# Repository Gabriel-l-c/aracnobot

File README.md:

# 🕷️ Aracnobot - Estrutura de Tarefas

## ⚡ Eletrônica & Código Embarcado (Hardware & Firmware)
- [ ] **Esquema e Layout (KiCad)**
  - [ ] Desenhar o esquemático elétrico (reguladores de tensão e distribuição de potência).
	- [ ] testar os servos e categorizar os angulos limites (para nunca travar em 0 ou 180, o servo nao
	pode travar!!!).
	- [ ] Testar as baterias, descarga, medir o sinal de alimentação da bateria ( tem picos? ruidos?), 
	para analisar necessidade de circuitos de filtro e proteção.
	- [ ] Circuito de BMS (sistema de gerenciamento de bateria), para controle de carregamento, descarga,
	, protecao contra sobrecarga e subtensao.
  - [ ] Fazer o layout da PCB no KiCad (trilhas largas para os servos e definição das pegadas/capacitores).
  - [ ] Gerar arquivos Gerber para fabricação da placa.
  * problemas:
	O banco de baterias disponivel sao 3s2p litio (3 baterias de litio em seria com 1 em parelelo para cada em serie
ou seja, 6 celulas, 3 pares), a descarga maxima das baterias deve ficar em 1.5C ( para uam bateria de 3Ah de capacidade, 
1.5 C =  4.5A de descarga maxima), cada celula tem 4V2 de tensão maxima e 1.5Ah de descarga. Logo, nao conseguimos
alcançar a potência (carga pesada e motores travados, todos sendo usados de uma vez). Dentro disso, temos que 
montar o firmware afim de nunca ultrapassar o consumo de 4.5A total, nao usar todas as patas de uma vez, carga leve, etc.

  - [ ] Circuito do regulador dos motores. Cuidados e problemas:
  A maior parte de potencia sera consumida pelos motores, logo e onde os reguladores vão trabalhar mais e onde mais energia
  sera transformada em calor. Logo, uma pesquisa de reguladores ideias para a carga de tensão de entrada e corrente de saida
  deve ser feita para iniciar o circuito. Reguladores sugestao: K7805, XL4015.
 
- [ ] **Configuração Inicial do Código**
  - [ ] Configurar ambiente de desenvolvimento (PlatformIO, Arduino IDE ou ESP-IDF).
  - [ ] Mapear os pinos físicos da PCB criada para as definições de variáveis no código.
- [ ] **Cinemática e Movimentação junto a equipe de estrutura**
  - [ ] Implementar algoritmo de Cinemática Inversa (IK) para as pernas.
  - [ ] Desenvolver padrões de marcha (Gait Patterns: tripé, onda, etc.).
  - [ ] Criar funções de estabilização corporal integrando sensor IMU/Giroscópio.
- [ ] **Comunicação, Telemetria & Proteção**
  - [ ] Configurar protocolo sem fio (Wi-Fi, Bluetooth ou ESP-NOW) para controle remoto.
  - [ ] Criar rotina de leitura de nível de bateria e alertas de subtensão para proteger as células LiPo.

## 📐 Estrutura Mecânica Física

## 👁️ Visão Computacional & Percepção

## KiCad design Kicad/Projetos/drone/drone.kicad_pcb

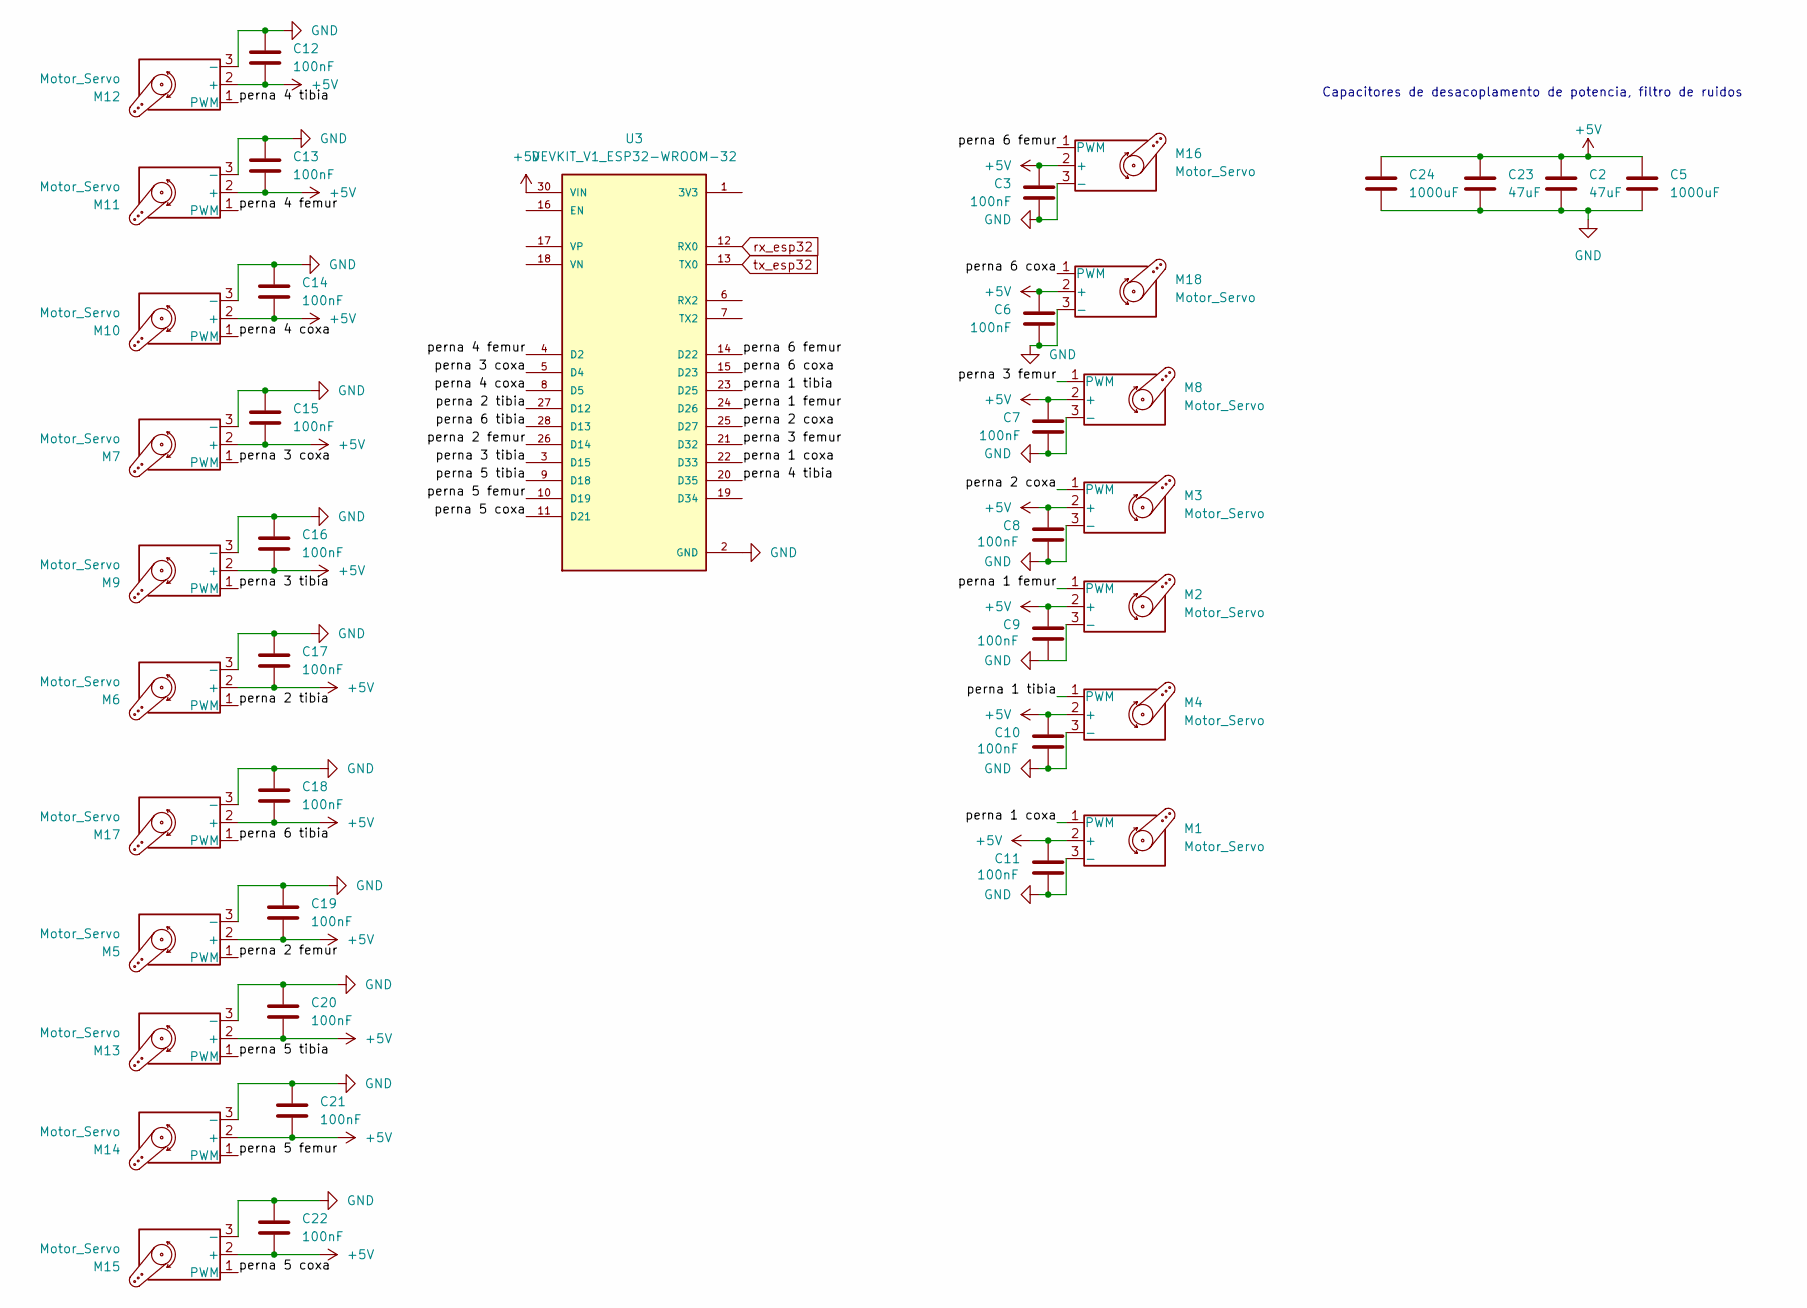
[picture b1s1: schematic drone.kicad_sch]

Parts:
C2, C23: 47uF; C_Disc_D7.0mm_W2.5mm_P5.00mm
C3, C6, C7, C8, C9, C10, C11, C12, C13, C14, C15, C16, C17, C18, C19, C20, C21, C22: 100nF; C_Disc_D7.0mm_W2.5mm_P5.00mm
C5, C24: 1000uF; C_Disc_D7.0mm_W2.5mm_P5.00mm
M1, M2, M3, M4, M5, M6, M7, M8, M9, M10, M11, M12, M13, M14, M15, M16, M17, M18: Motor_Servo; PinHeader_1x03_P2.54mm_Vertical
U3: DEVKIT_V1_ESP32-WROOM-32; MODULE_DEVKIT_V1_ESP32-WROOM-32

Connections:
+5V: C2.1, C3.1, C5.1, C6.1, C7.1, C8.1, C9.1, C10.1, C11.1, C12.2, C13.2, C14.2, C15.2, C16.2, C17.2, C18.2, C19.2, C20.2, C21.2, C22.2, C23.1, C24.1, M1.2 (+), M2.2 (+), M3.2 (+), M4.2 (+), M5.2 (+), M6.2 (+), M7.2 (+), M8.2 (+), M9.2 (+), M10.2 (+), M11.2 (+), M12.2 (+), M13.2 (+), M14.2 (+), M15.2 (+), M16.2 (+), M17.2 (+), M18.2 (+), U3.30 (VIN); also elsewhere on the board
/Raiz/perna 1 coxa: M1.1 (PWM), U3.22 (D33)
/Raiz/perna 1 femur: M2.1 (PWM), U3.24 (D26)
/Raiz/perna 1 tibia: M4.1 (PWM), U3.23 (D25)
/Raiz/perna 2 coxa: M3.1 (PWM), U3.25 (D27)
/Raiz/perna 2 femur: M5.1 (PWM), U3.26 (D14)
/Raiz/perna 2 tibia: M6.1 (PWM), U3.27 (D12)
/Raiz/perna 3 coxa: M7.1 (PWM), U3.5 (D4)
/Raiz/perna 3 femur: M8.1 (PWM), U3.21 (D32)
/Raiz/perna 3 tibia: M9.1 (PWM), U3.3 (D15)
/Raiz/perna 4 coxa: M10.1 (PWM), U3.8 (D5)
/Raiz/perna 4 femur: M11.1 (PWM), U3.4 (D2)
/Raiz/perna 4 tibia: M12.1 (PWM), U3.20 (D35)
/Raiz/perna 5 coxa: M15.1 (PWM), U3.11 (D21)
/Raiz/perna 5 femur: M14.1 (PWM), U3.10 (D19)
/Raiz/perna 5 tibia: M13.1 (PWM), U3.9 (D18)
/Raiz/perna 6 coxa: M18.1 (PWM), U3.15 (D23)
/Raiz/perna 6 femur: M16.1 (PWM), U3.14 (D22)
/Raiz/perna 6 tibia: M17.1 (PWM), U3.28 (D13)
GND: C2.2, C3.2, C5.2, C6.2, C7.2, C8.2, C10.2, C11.2, C12.1, C13.1, C14.1, C15.1, C16.1, C17.1, C18.1, C19.1, C20.1, C21.1, C22.1, C23.2, C24.2, M1.3 (-), M2.3 (-), M3.3 (-), M4.3 (-), M5.3 (-), M6.3 (-), M7.3 (-), M8.3 (-), M9.3 (-), M10.3 (-), M11.3 (-), M12.3 (-), M13.3 (-), M14.3 (-), M15.3 (-), M16.3 (-), M17.3 (-), M18.3 (-), U3.2 (GND), U3.29 (GND); also elsewhere on the board
rx_esp32: U3.12 (RX0); also elsewhere on the board
tx_esp32: U3.13 (TX0); also elsewhere on the board

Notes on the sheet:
Capacitores de desacoplamento de potencia, filtro de ruidos

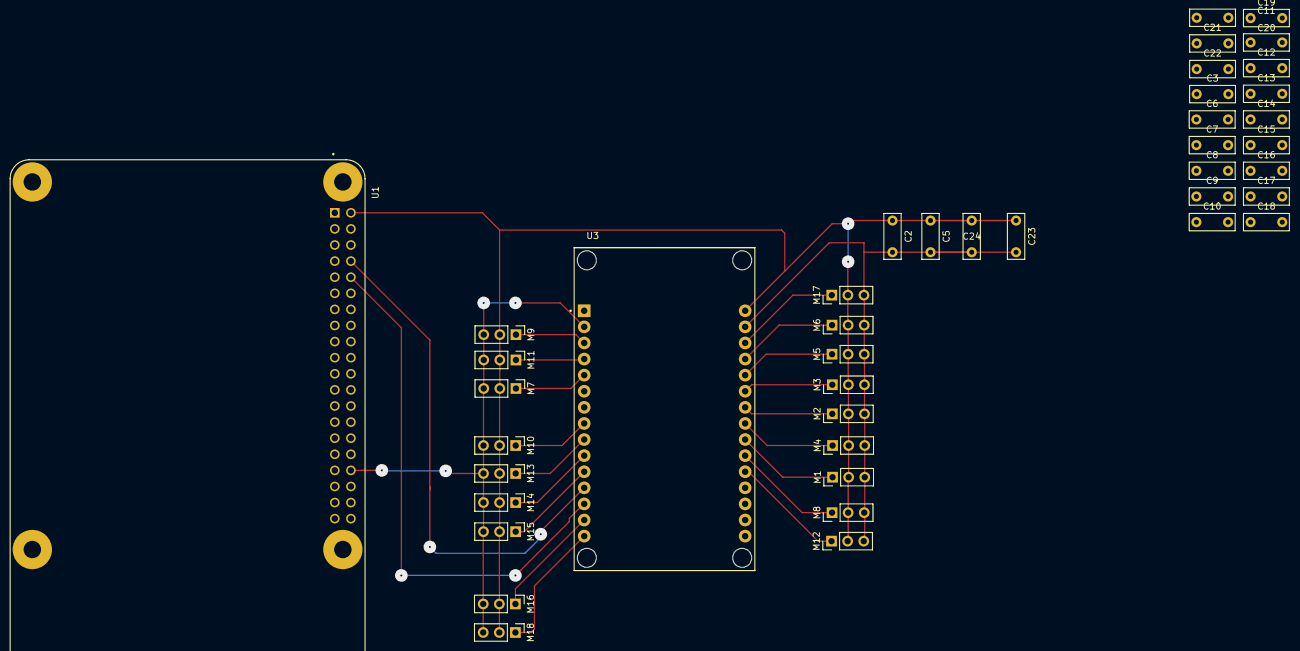
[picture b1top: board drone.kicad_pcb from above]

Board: 2 copper layers, 42 parts (0 on the bottom side), 24 nets.

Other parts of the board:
U1: SC0195_9_; MODULE_SRASPBERRY_PI_4_MODEL_B_

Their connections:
3V3: U1.1 (3V3), U1.17 (3V3)
+5V: U1.2 (5V0), U1.4 (5V0); also elsewhere on the board
GND: U1.6 (GND), U1.9 (GND), U1.14 (GND), U1.20 (GND), U1.25 (GND), U1.30 (GND), U1.34 (GND), U1.39 (GND); also elsewhere on the board
SHIELD: U1.S1 (SHIELD), U1.S2 (SHIELD), U1.S3 (SHIELD), U1.S4 (SHIELD)
rx_esp32: U1.8 (TXD0/GPIO14); also elsewhere on the board
tx_esp32: U1.10 (RXD0/GPIO15); also elsewhere on the board

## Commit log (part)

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2026-05-28 cronograma e planejamento
2026-05-29 Revise README for ArachnoBot Rescue project details
    Updated README.md to include project overview, objectives, technical foundation, and references for the ArachnoBot Rescue UGV.
2026-05-29 Update quote formatting in README
    Reformat quote for better readability
2026-05-29 Remove bibliographic references section
    Removed bibliographic references section from README.
2026-05-29 referencias
2026-05-29 Expand README with study areas and applications
    Added sections on areas of study and application related to embedded systems, communication networks, robotics, computer vision, and power electronics.
2026-06-04 Revise project overview and focus areas in README
    Expanded project description and clarified focus areas.
2026-06-11 atuaizacao
2026-06-15 kicad
2026-06-15 model 4 B
2026-06-15 Pasta de datasheet
2026-06-16 alguns datasheets
2026-06-18 setup do docker + pacote teste vazio do ros
